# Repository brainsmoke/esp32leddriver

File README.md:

# LED Driver for 3D sculptures based on an ESP32 with PSRAM + an STM32F0XX

# Design:

```
   programming &
  micropython REPL
         ||
     .--------.
     |  usb   |
     |   to   |
     | serial | 
     '--------'
         ||
   .--------------.                               _____________.--
   |  ESP32-D0WD  |          (UART)              |             |-- multiple LED strands
   |   8M PSRAM   |-- 16bit/color LED frames --> |  STM32F0XX  |-- (temporal dithered)
   |  16M FLASH   |                              |_____________|--
   '--------------'                                            '--

```

# ESP Code `firmware/esp32/`

- Running micropython

- 60 FPS 16bit/color (48bit) animation with some routines written in C for speed.

- Animations use 3D-coordinates of the LEDs, as well as the direction they're pointing at

- Gamma correction & support for multiple LED orderings.

- Cached animation frames to prevent garbage collection hiccups

- Web interface (HTTPS capable, but no automatic cert. updates)

# STM32 Code `firmware/stm32/`

## Protocol

Sending a frame: `( [16 bit brightness]* [ FF FF FF F0 ] )*`

Brightness must be little endian integers in the (inclusive) range `[0 .. 0xFF00]`

`[ FF FF FF F0 ]` is an end of frame marker and allows the protocol to synchronize
in the event of an uneven number of bytes being written to the serial port

The firmware is completely agnostic about the color ordering.

Some of the following firmwares allow for tuning of the pulse interval:

`( [16 bit number]* [ FF FF FF F3 ] )*`

The given number is the number of cycles outputting a byte should take.
(Useful for increasing the FPS and thus improving temporal dithering.

## `dither16.bin`

Read in 16bit/color data in, drive 8 ws2812 LED strips in parallel

## `strip4.bin`

Read in 16bit/color data in, drive 4 ws2812 LED strips in parallel

## `strip5.bin`

Read in 16bit/color data in, drive 5 ws2812 LED strips in parallel,
Supports tuning the pulse interval.

## `relayball.bin`

Read in 16bit/color data in, drive 4 circuit-routed ws2812 LED meshes.
Small LED strands are connected through PADAUK based relay-chips
(`firmware/pdk/relay/`) that use in-band messages to build up routing
circuits.

## `uartball16.bin`

Drives up-to 8 busses with PADAUK based LED drivers which read 38400 baud
uart. `firmware/pdk/softpwm/`

##  `dither8.bin`

Older code using a different input protocol, reads 8bit/color data & transforms this to 16 bit colors
after gamma correction

# STM32 Tester code

## `jitter_timer.bin`

Tester for PADAUK ws2812 relay chips. `firmware/pdk/relay/`

Tests for functionality and measures the clock speed deviation (for binning).

## `timing_experiment.bin`

Dynamically adjust the `T1H` and `T1L` intervals from the ws2812 protocol to
test its limits.

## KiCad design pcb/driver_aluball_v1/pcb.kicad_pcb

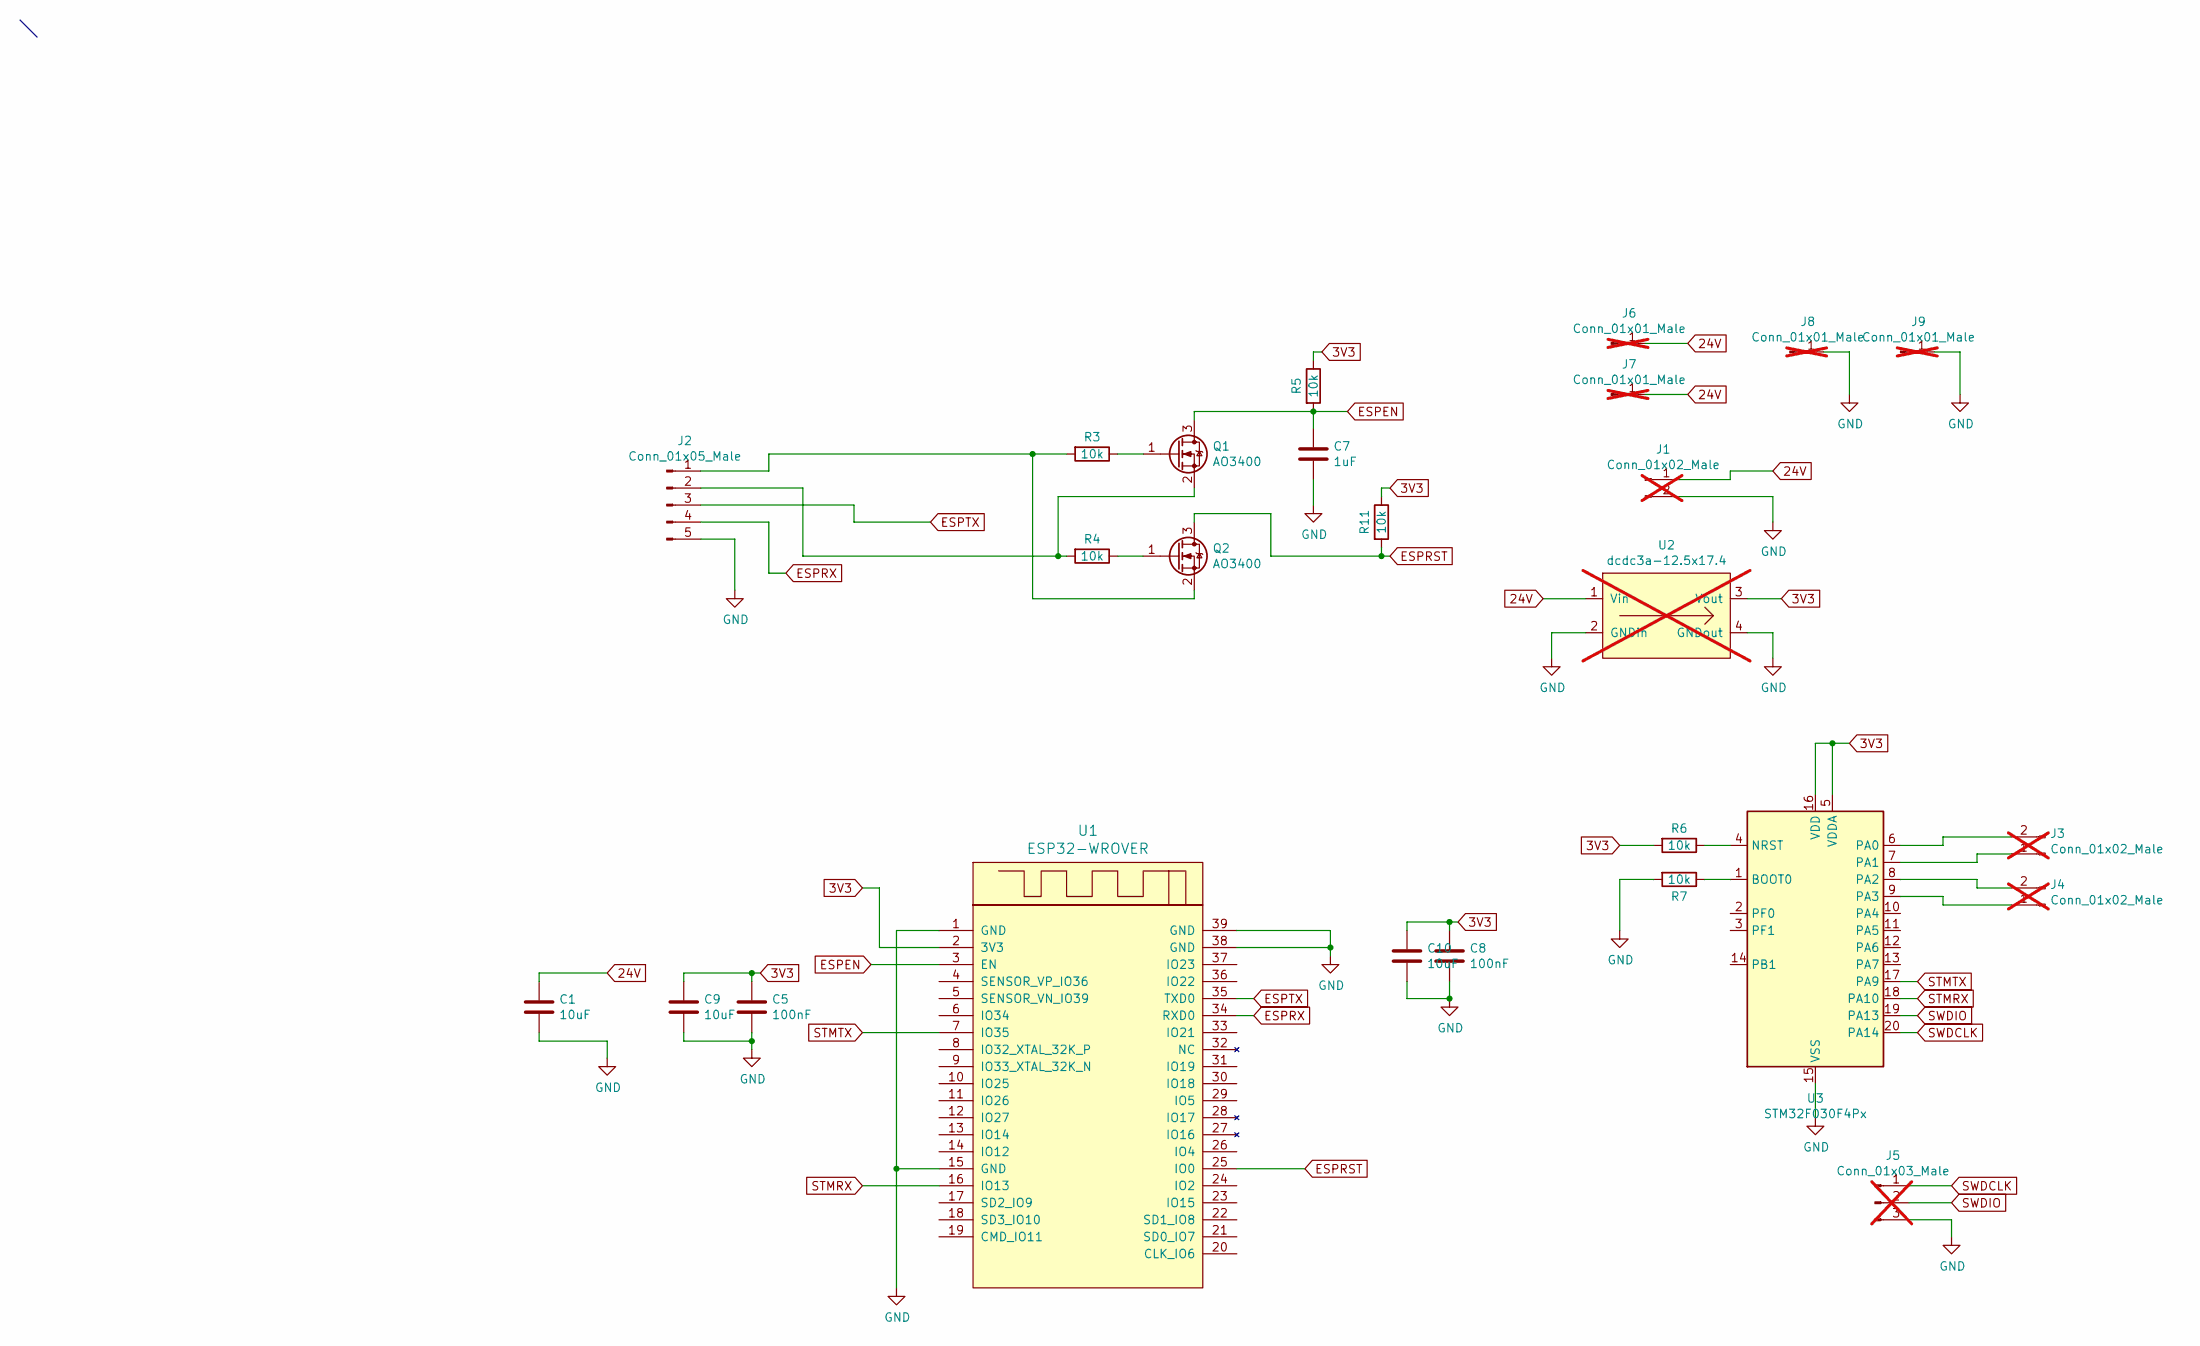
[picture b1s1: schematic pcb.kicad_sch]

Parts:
C1, C9, C10: 10uF; C_1206_3216Metric; LCSC C13585
C5, C8: 100nF; C_0402_1005Metric; LCSC C1525
C7: 1uF; C_0402_1005Metric; LCSC C52923
J1: Conn_01x02_Male; xt60-pcb; not fitted
J2: Conn_01x05_Male; Molex_PicoBlade_53261-0571_1x05-1MP_P1.25mm_Horizontal; LCSC C225114
J3, J4: Conn_01x02_Male; PinHeader_1x02_P2.54mm_Vertical; not fitted
J5: Conn_01x03_Male; PinHeader_1x03_P2.54mm_Vertical; not fitted
J6, J7, J8, J9: Conn_01x01_Male; solderpad1; not fitted
Q1, Q2: AO3400; SOT-23; LCSC C20917
R3, R4, R5, R6, R7, R11: 10k; R_0402_1005Metric; LCSC C25744
U1: ESP32-WROVER; XCVR_ESP32-WROVER; LCSC C701352
U2: dcdc3a-12.5x17.4; not fitted
U3: STM32F030F4Px; TSSOP-20_4.4x6.5mm_P0.65mm; LCSC C89040

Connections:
3V3: C5.1, C8.1, C9.1, C10.1, R5.1, R6.2, R11.1, U1.2 (3V3), U2.3 (Vout), U3.5 (VDDA), U3.16 (VDD)
24V: C1.1, J1.1, J6.1, J7.1, U2.1 (Vin)
ESPEN: C7.1, Q1.3 (D), R5.2, U1.3 (EN)
ESPRST: Q2.3 (D), R11.2, U1.25 (IO0)
ESPRX: J2.4, U1.34 (RXD0)
ESPTX: J2.3, U1.35 (TXD0)
GND: C1.2, C5.2, C7.2, C8.2, C9.2, C10.2, J1.2, J2.5, J5.3, J8.1, J9.1, R7.2, U1.1 (GND), U1.15 (GND), U1.38 (GND), U1.39 (GND), U2.2 (GNDin), U2.4 (GNDout), U3.15 (VSS)
unnamed: J2.1, Q2.2 (S), R3.2
unnamed: J2.2, Q1.2 (S), R4.2
unnamed: J3.1, U3.7 (PA1)
unnamed: J3.2, U3.6 (PA0)
unnamed: J4.1, U3.9 (PA3)
unnamed: J4.2, U3.8 (PA2)
unnamed: Q1.1 (G), R3.1
unnamed: Q2.1 (G), R4.1
unnamed: R7.1, U3.1 (BOOT0)
unnamed: R6.1, U3.4 (NRST)
STMRX: U1.16 (IO13), U3.18 (PA10)
STMTX: U1.7 (IO35), U3.17 (PA9)
SWDCLK: J5.1, U3.20 (PA14)
SWDIO: J5.2, U3.19 (PA13)

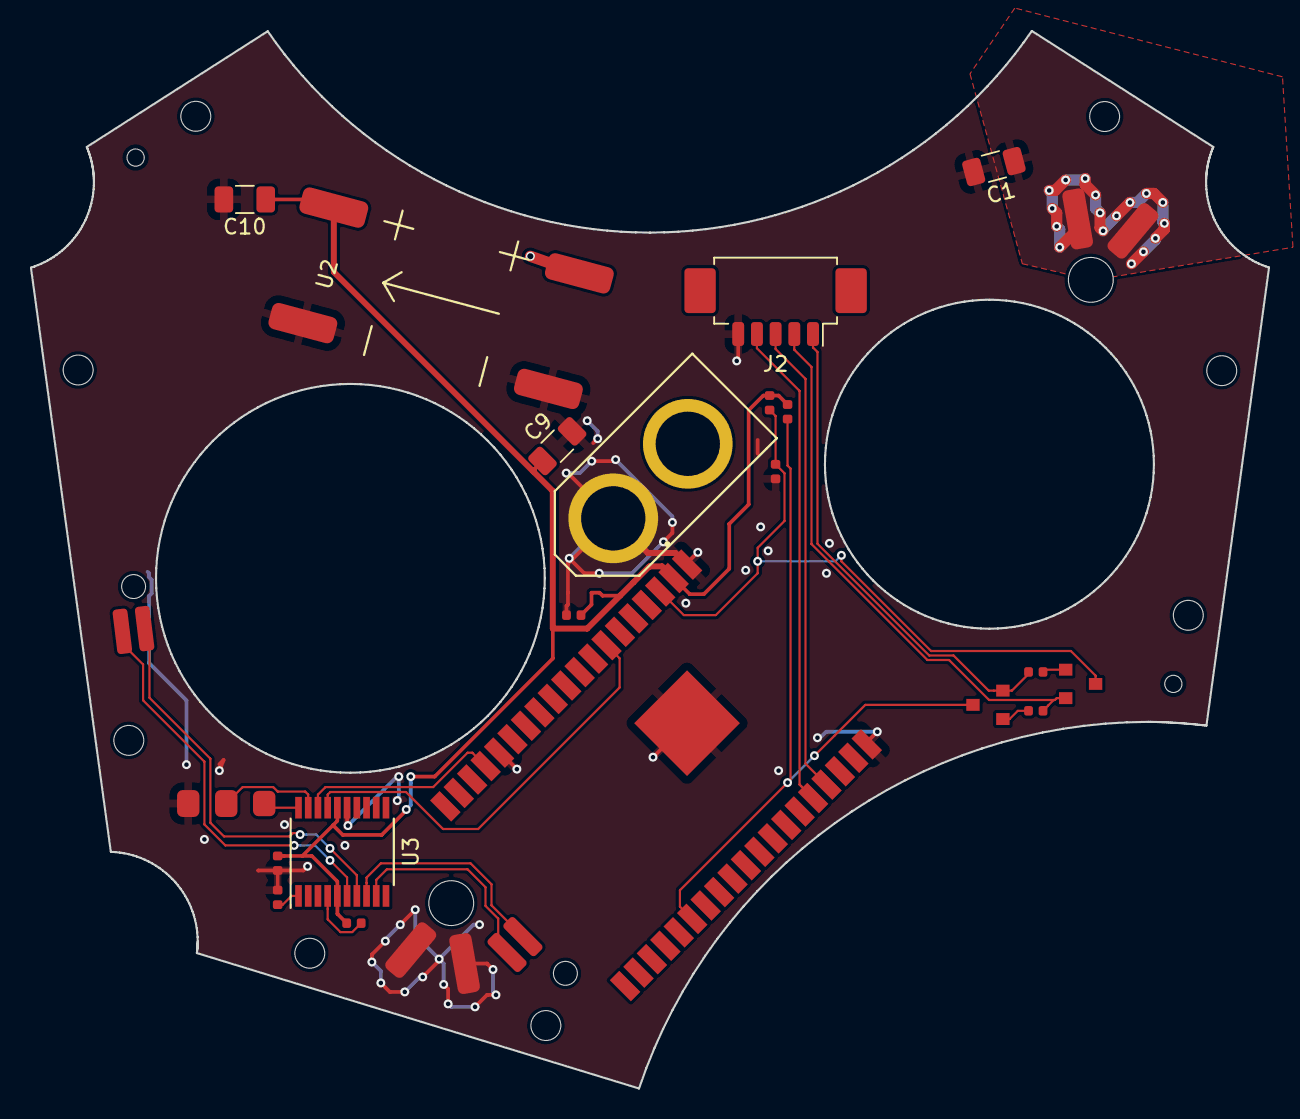
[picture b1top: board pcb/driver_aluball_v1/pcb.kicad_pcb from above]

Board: 2 copper layers, 82.8 x 70.7 mm, 26 parts (0 on the bottom side), 21 nets.

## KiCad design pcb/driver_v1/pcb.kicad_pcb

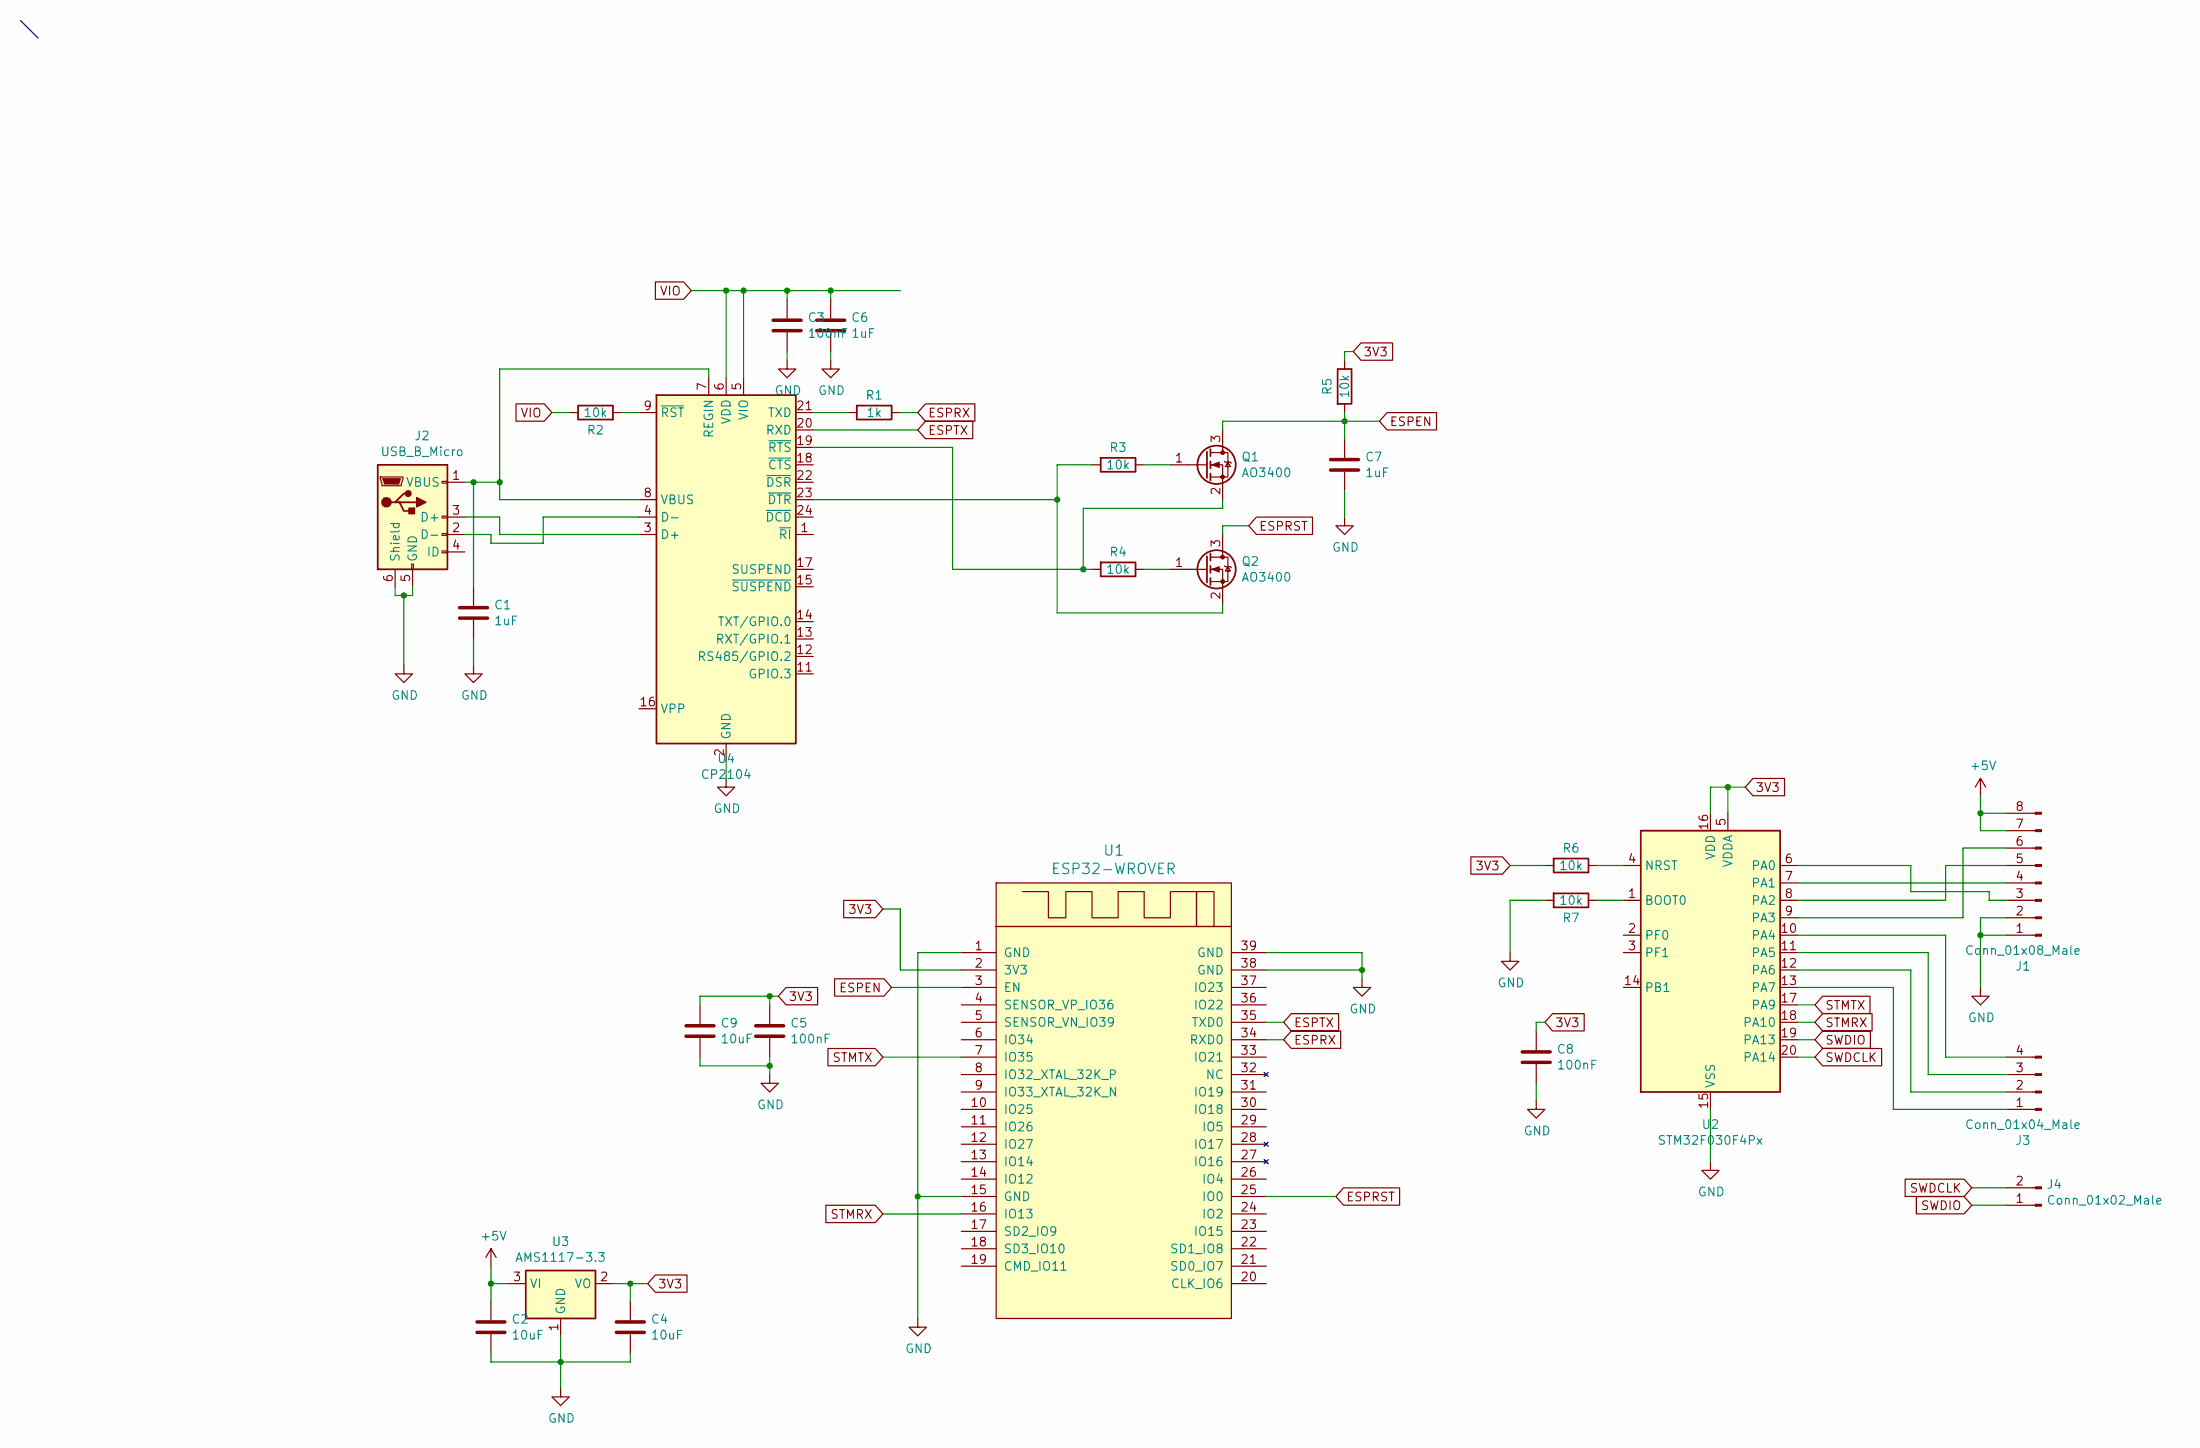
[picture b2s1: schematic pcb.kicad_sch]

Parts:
C1, C6, C7: 1uF; C_0603_1608Metric; LCSC C15849
C2, C4, C9: 10uF; C_0603_1608Metric; LCSC C15850
C3, C5, C8: 100nF; C_0603_1608Metric; LCSC C14663
J1: Conn_01x08_Male; PinHeader_1x08_P2.54mm_Vertical
J2: USB_B_Micro; USB_Micro-B_Molex_47346-0001
J3: Conn_01x04_Male; PinHeader_1x04_P2.54mm_Vertical
J4: Conn_01x02_Male; PinHeader_1x02_P2.54mm_Vertical
Q1, Q2: AO3400; SOT-23; LCSC C20917
R1: 1k; R_0603_1608Metric_nolabel; LCSC C21190
R2, R3, R4, R5, R6, R7: 10k; R_0603_1608Metric_nolabel; LCSC C25804
U1: ESP32-WROVER; XCVR_ESP32-WROVER
U2: STM32F030F4Px; TSSOP-20_4.4x6.5mm_P0.65mm; LCSC C89040
U3: AMS1117-3.3; SOT-223-3_TabPin2; LCSC C6186
U4: CP2104; QFN-24-1EP_4x4mm_P0.5mm_EP2.6x2.6mm; LCSC C47742

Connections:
3V3: C4.1, C5.1, C8.1, C9.1, R5.1, R6.2, U1.2 (3V3), U2.5 (VDDA), U2.16 (VDD), U3.2 (VO)
+5V: C2.1, J1.7, J1.8, U3.3 (VI)
ESPEN: C7.1, Q1.3 (D), R5.2, U1.3 (EN)
ESPRST: Q2.3 (D), U1.25 (IO0)
ESPRX: R1.1, U1.34 (RXD0)
ESPTX: U1.35 (TXD0), U4.20 (RXD)
GND: C1.2, C2.2, C3.2, C4.2, C5.2, C6.2, C7.2, C8.2, C9.2, J1.1, J1.2, J2.5 (GND), J2.6 (Shield), R7.2, U1.1 (GND), U1.15 (GND), U1.38 (GND), U1.39 (GND), U2.15 (VSS), U3.1 (GND), U4.2 (GND), U4.25 (GND)
unnamed: J1.3, U2.6 (PA0)
unnamed: J1.4, U2.7 (PA1)
unnamed: J1.5, U2.8 (PA2)
unnamed: J1.6, U2.9 (PA3)
unnamed: J2.3 (D+), U4.3 (D+)
unnamed: J2.2 (D-), U4.4 (D-)
unnamed: C1.1, J2.1 (VBUS), U4.7 (REGIN), U4.8 (VBUS)
unnamed: J3.1, U2.13 (PA7)
unnamed: J3.2, U2.12 (PA6)
unnamed: J3.3, U2.11 (PA5)
unnamed: J3.4, U2.10 (PA4)
unnamed: Q1.1 (G), R3.1
unnamed: Q1.2 (S), R4.2, U4.19 (~RTS)
unnamed: Q2.1 (G), R4.1
unnamed: Q2.2 (S), R3.2, U4.23 (~DTR)
unnamed: R7.1, U2.1 (BOOT0)
unnamed: R6.1, U2.4 (NRST)
unnamed: R1.2, U4.21 (TXD)
unnamed: R2.2, U4.9 (~RST)
STMRX: U1.16 (IO13), U2.18 (PA10)
STMTX: U1.7 (IO35), U2.17 (PA9)
SWDCLK: J4.2, U2.20 (PA14)
SWDIO: J4.1, U2.19 (PA13)
VIO: C3.1, C6.1, R2.1, U4.5 (VIO), U4.6 (VDD)

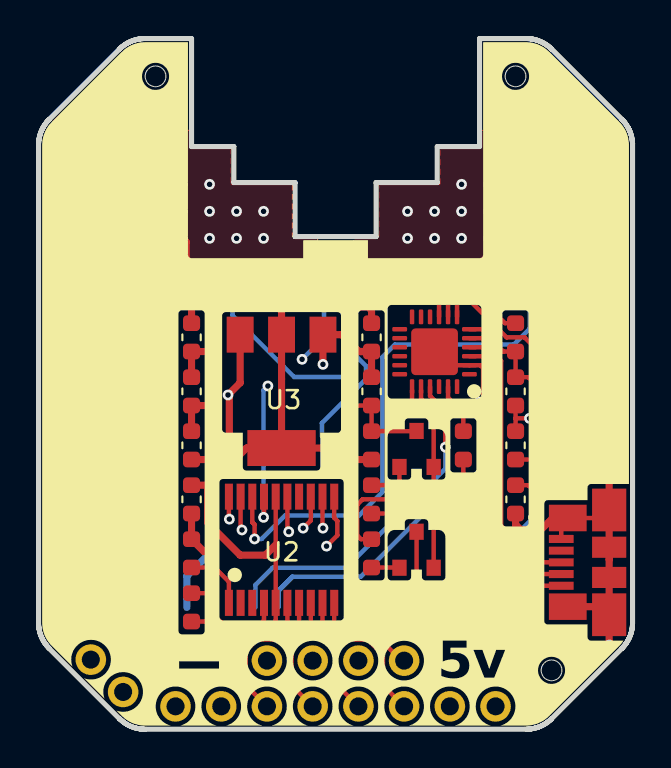
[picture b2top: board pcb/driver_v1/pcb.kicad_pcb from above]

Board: 4 copper layers, 33.0 x 38.4 mm, 26 parts (1 on the bottom side), 31 nets.

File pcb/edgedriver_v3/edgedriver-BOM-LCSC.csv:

Comment,Designator,Footprint,LCSC Part Number
"10uF","C4,C2,C9","0603","C19702"
"1uF","C7,C6,C1","0603","C15849"
"100nF","C8,C5,C3","0603","C14663"
"AO3400","Q1,Q2","SOT-23-3L","C20917"
"1k","R1","0603","C21190"
"10k","R6,R7,R3,R4,R5,R2","0603","C25804"
"STM32F030F4P6","U2","TSSOP-20_4.4x6.5x0.65P","C89040"
"AMS1117-3.3","U3","SOT-223","C6186"
"CP2104","U4","QFN-24_EP_4.0x4.0x0.5P","C47742"

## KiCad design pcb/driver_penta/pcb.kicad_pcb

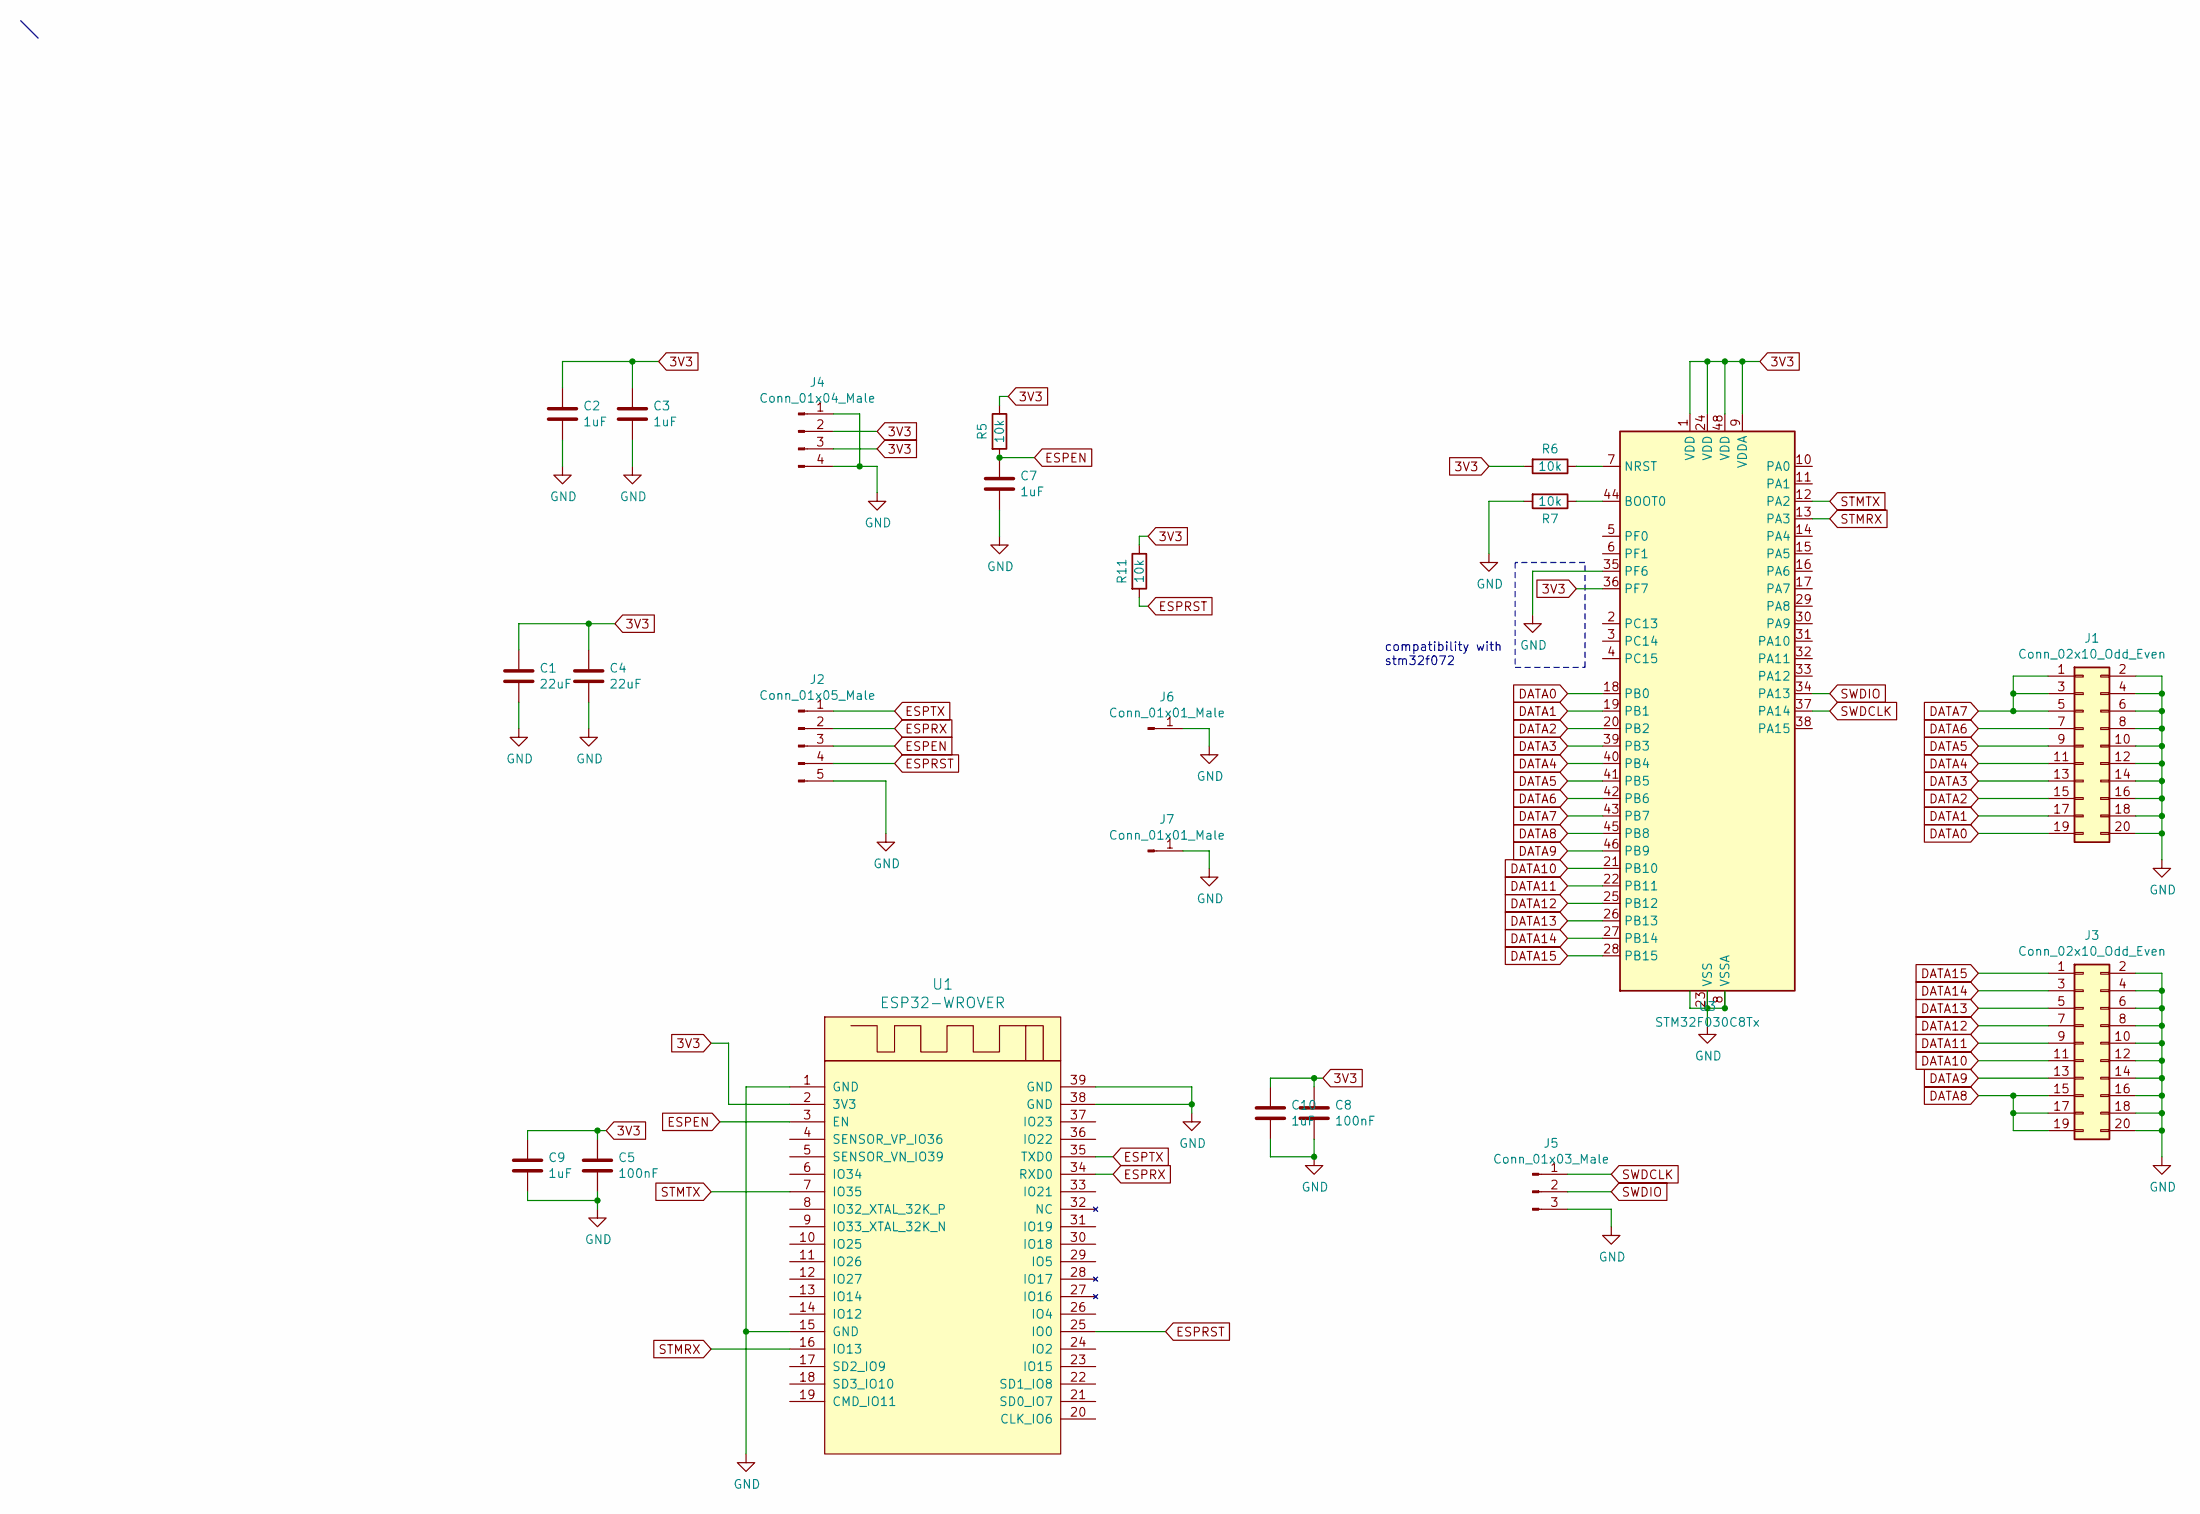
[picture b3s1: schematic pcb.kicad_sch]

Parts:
C1, C4: 22uF; C_1210_3225Metric; LCSC C52923
C2, C3, C7, C9, C10: 1uF; C_0402_1005Metric; LCSC C52923
C5, C8: 100nF; C_0402_1005Metric; LCSC C1525
J1, J3: Conn_02x10_Odd_Even; PinHeader_2x10_P2.54mm_Vertical
J2: Conn_01x05_Male; Molex_PicoBlade_53261-0571_1x05-1MP_P1.25mm_Horizontal; LCSC C225114
J4: Conn_01x04_Male; PinHeader_1x04_P2.54mm_Vertical
J5: Conn_01x03_Male; PinHeader_1x03_P2.54mm_Vertical
J6, J7: Conn_01x01_Male; PinHeader_1x01_P2.54mm_Vertical
R5, R6, R7, R11: 10k; R_0402_1005Metric; LCSC C25744
U1: ESP32-WROVER; XCVR_ESP32-WROVER; LCSC C701352
U3: STM32F030C8Tx; LQFP-48_7x7mm_P0.5mm; LCSC C23922

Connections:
3V3: C1.1, C2.1, C3.1, C4.1, C5.1, C8.1, C9.1, C10.1, J4.2, J4.3, R5.1, R6.2, R11.1, U1.2 (3V3), U3.1 (VDD), U3.9 (VDDA), U3.24 (VDD), U3.36 (PF7), U3.48 (VDD)
DATA0: J1.19, U3.18 (PB0)
DATA1: J1.17, U3.19 (PB1)
DATA2: J1.15, U3.20 (PB2)
DATA3: J1.13, U3.39 (PB3)
DATA4: J1.11, U3.40 (PB4)
DATA5: J1.9, U3.41 (PB5)
DATA6: J1.7, U3.42 (PB6)
DATA7: J1.1, J1.3, J1.5, U3.43 (PB7)
DATA8: J3.15, J3.17, J3.19, U3.45 (PB8)
DATA9: J3.13, U3.46 (PB9)
DATA10: J3.11, U3.21 (PB10)
DATA11: J3.9, U3.22 (PB11)
DATA12: J3.7, U3.25 (PB12)
DATA13: J3.5, U3.26 (PB13)
DATA14: J3.3, U3.27 (PB14)
DATA15: J3.1, U3.28 (PB15)
ESPEN: C7.1, J2.3, R5.2, U1.3 (EN)
ESPRST: J2.4, R11.2, U1.25 (IO0)
ESPRX: J2.2, U1.34 (RXD0)
ESPTX: J2.1, U1.35 (TXD0)
GND: C1.2, C2.2, C3.2, C4.2, C5.2, C7.2, C8.2, C9.2, C10.2, J1.2, J1.4, J1.6, J1.8, J1.10, J1.12, J1.14, J1.16, J1.18, J1.20, J2.5, J3.2, J3.4, J3.6, J3.8, J3.10, J3.12, J3.14, J3.16, J3.18, J3.20, J4.1, J4.4, J5.3, J6.1, J7.1, R7.2, U1.1 (GND), U1.15 (GND), U1.38 (GND), U1.39 (GND), U3.8 (VSSA), U3.23 (VSS), U3.35 (PF6), U3.47 (VSS)
unnamed: R7.1, U3.44 (BOOT0)
unnamed: R6.1, U3.7 (NRST)
STMRX: U1.16 (IO13), U3.13 (PA3)
STMTX: U1.7 (IO35), U3.12 (PA2)
SWDCLK: J5.1, U3.37 (PA14)
SWDIO: J5.2, U3.34 (PA13)

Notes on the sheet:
compatibility with stm32f072

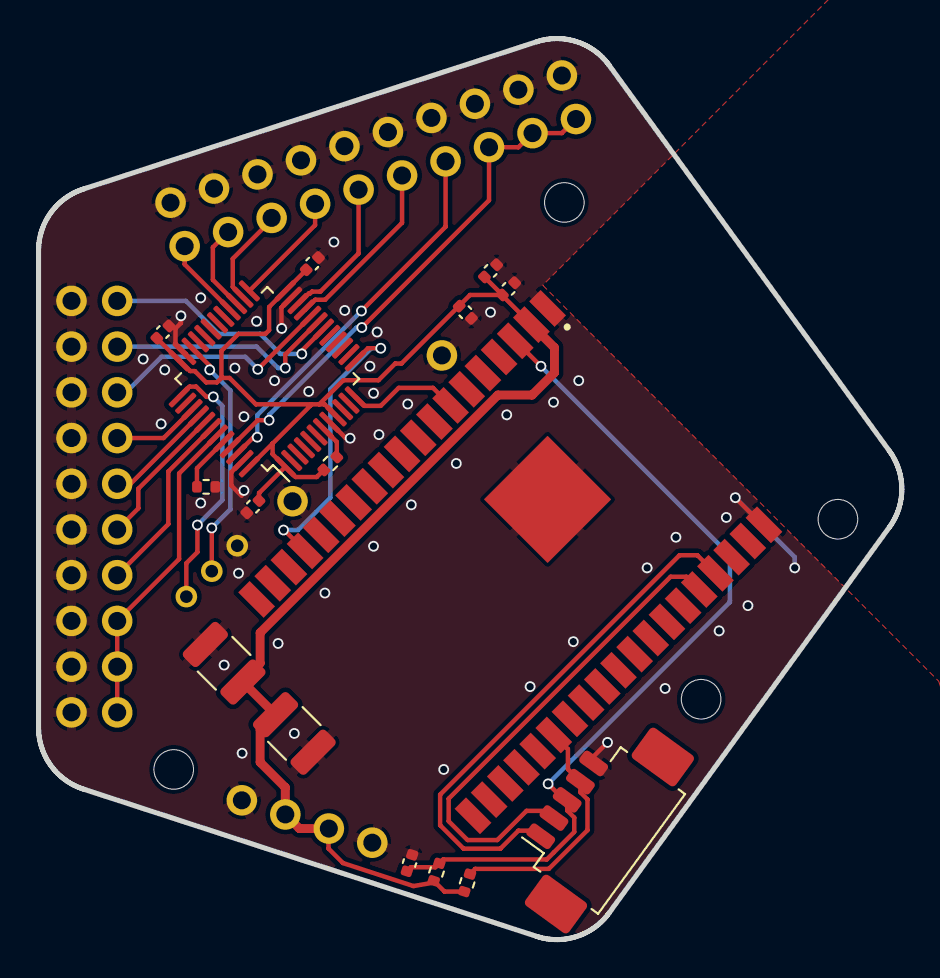
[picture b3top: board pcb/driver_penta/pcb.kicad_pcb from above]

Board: 2 copper layers, 48.0 x 50.1 mm, 22 parts (0 on the bottom side), 28 nets.

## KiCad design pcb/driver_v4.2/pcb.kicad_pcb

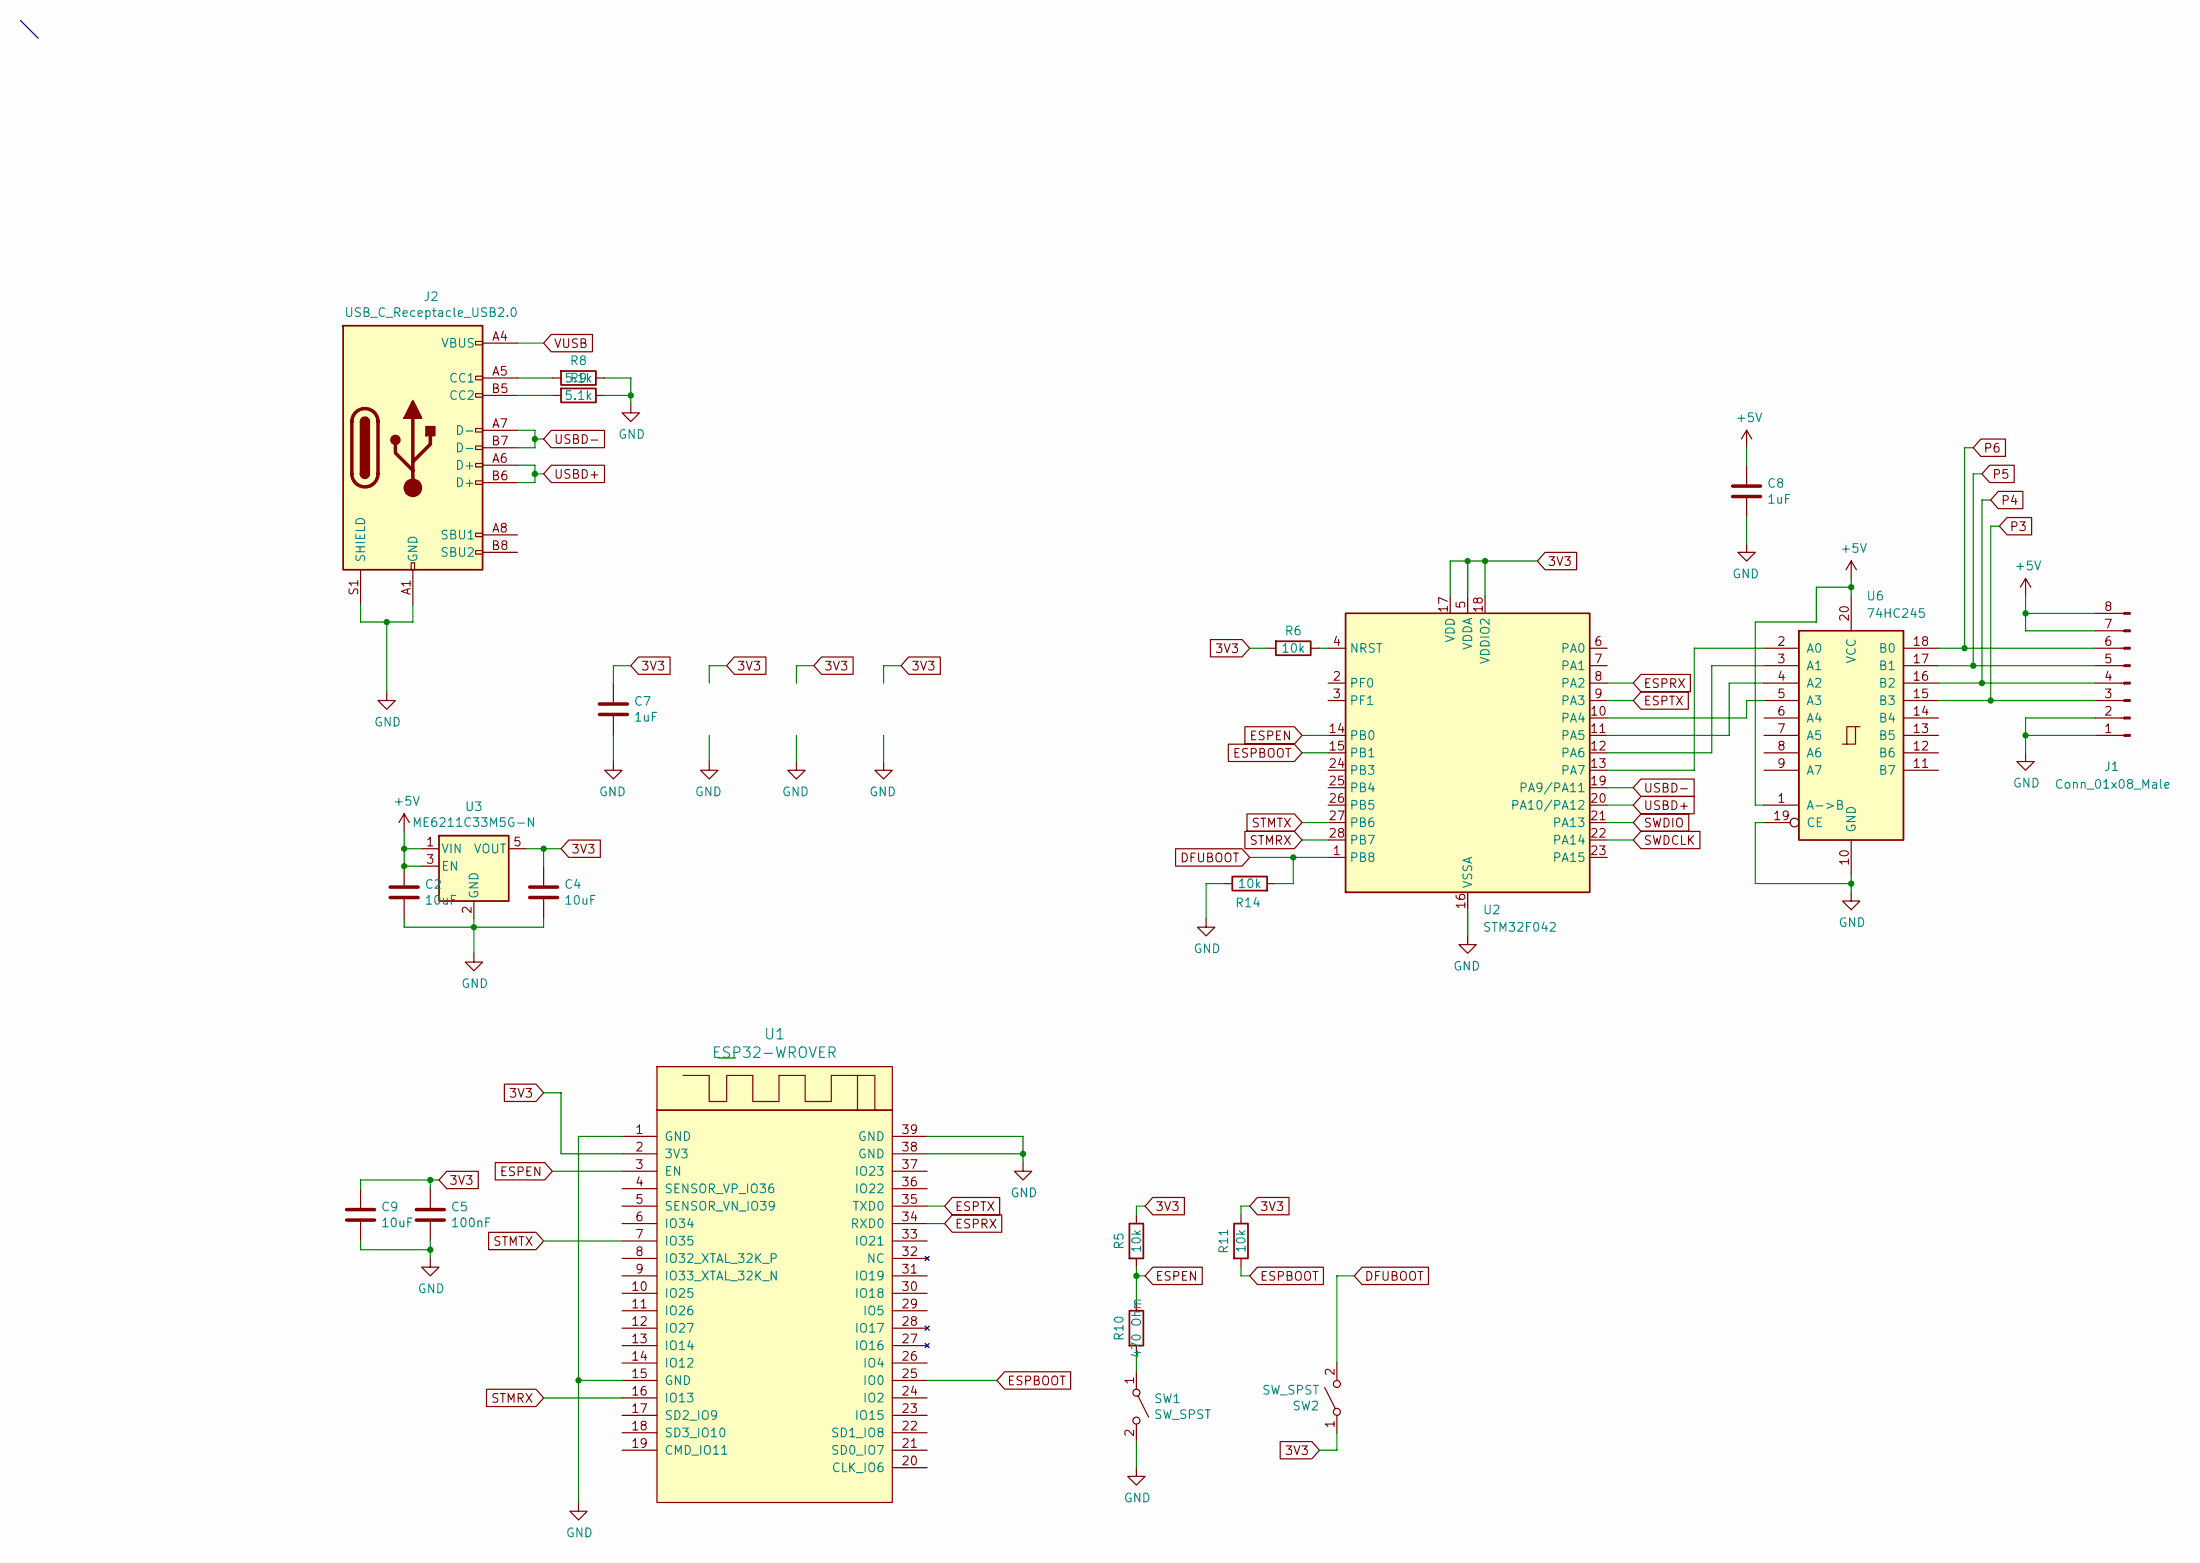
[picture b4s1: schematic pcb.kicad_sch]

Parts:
C2, C4, C9: 10uF; C_0603_1608Metric; LCSC C19702
C5: 100nF; C_0402_1005Metric; LCSC C1525
C7, C8: 1uF; C_0402_1005Metric; LCSC C52923
J1: Conn_01x08_Male; PinHeader_1x08_P2.54mm_Vertical
J2: USB_C_Receptacle_USB2.0; USB_C_Receptacle_HRO_TYPE-C-31-M-12; LCSC C165948
R5, R6, R11, R14: 10k; R_0402_1005Metric; LCSC C25744
R8, R9: 5.1k; R_0402_1005Metric; LCSC C25905
R10: 470 Ohm; R_0402_1005Metric; LCSC C25117
SW1, SW2: SW_SPST; SW_Push_1P1T_NO_CK_KMR2; LCSC C318893
U1: ESP32-WROVER; XCVR_ESP32-WROVER
U2: STM32F042; QFN-28_4x4mm_P0.5mm
U3: ME6211C33M5G-N; SOT-23-5; LCSC C82942
U6: 74HC245; DHVQFN-20-1EP_2.5x4.5mm_P0.5mm_EP1x3mm

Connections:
3V3: C4.1, C5.1, C7.1, C9.1, R5.1, R6.2, R11.1, SW2.1 (A), U1.2 (3V3), U2.5 (VDDA), U2.17 (VDD), U2.18 (VDDIO2), U3.5 (VOUT)
+5V: C2.1, C8.1, J1.7, J1.8, U3.1 (VIN), U3.3 (EN), U6.1 (A->B), U6.20 (VCC)
DFUBOOT: R14.2, SW2.2 (B), U2.1 (PB8)
ESPBOOT: R11.2, U1.25 (IO0), U2.15 (PB1)
ESPEN: R5.2, R10.1, U1.3 (EN), U2.14 (PB0)
ESPRX: U1.34 (RXD0), U2.8 (PA2)
ESPTX: U1.35 (TXD0), U2.9 (PA3)
GND: C2.2, C4.2, C5.2, C7.2, C8.2, C9.2, J1.1, J1.2, J2.A1 (GND), J2.A12 (GND), J2.B1 (GND), J2.B12 (GND), J2.S1 (SHIELD), R8.1, R9.1, R14.1, SW1.2 (B), U1.1 (GND), U1.15 (GND), U1.38 (GND), U1.39 (GND), U2.16 (VSSA), U3.2 (GND), U6.10 (GND), U6.19 (CE)
unnamed: J2.A5 (CC1), R8.2
unnamed: J2.B5 (CC2), R9.2
unnamed: R10.2, SW1.1 (A)
unnamed: R6.1, U2.4 (NRST)
unnamed: U2.10 (PA4), U6.5 (A3)
unnamed: U2.11 (PA5), U6.4 (A2)
unnamed: U2.12 (PA6), U6.3 (A1)
unnamed: U2.13 (PA7), U6.2 (A0)
P3: J1.3, U6.15 (B3)
P4: J1.4, U6.16 (B2)
P5: J1.5, U6.17 (B1)
P6: J1.6, U6.18 (B0)
STMRX: U1.16 (IO13), U2.28 (PB7)
STMTX: U1.7 (IO35), U2.27 (PB6)
SWDCLK: U2.22 (PA14)
SWDIO: U2.21 (PA13)
USBD+: J2.A6 (D+), J2.B6 (D+), U2.20 (PA10/PA12)
USBD-: J2.A7 (D-), J2.B7 (D-), U2.19 (PA9/PA11)
VUSB: J2.A4 (VBUS), J2.A9 (VBUS), J2.B4 (VBUS), J2.B9 (VBUS)

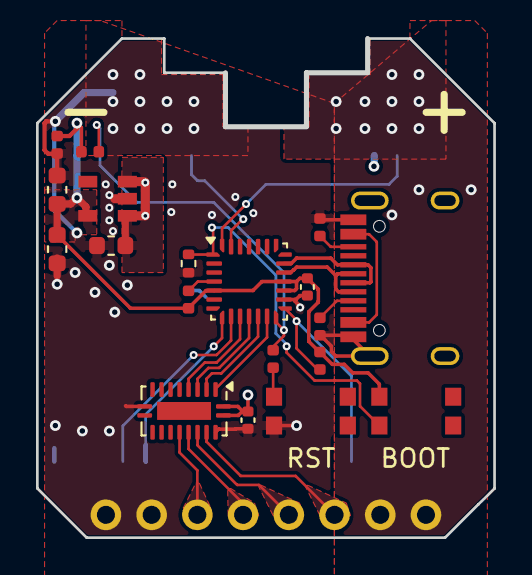
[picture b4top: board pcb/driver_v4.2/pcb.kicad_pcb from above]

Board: 4 copper layers, 25.4 x 27.7 mm, 21 parts (1 on the bottom side), 25 nets.
